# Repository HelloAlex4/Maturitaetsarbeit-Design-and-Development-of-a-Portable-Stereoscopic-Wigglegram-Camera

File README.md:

# Design and Development of a Portable Stereoscopic Wigglegram Camera

### !!!THIS IS NOT THE CURRENT VERSION OF MERGED.CAMERA, YOU SHOULD NOT COPY THIS BUILD!!!

**Author:** Alexander Rieser

**Project Type:** Maturitätsarbeit (25/26)

**Supervisor:** Madlaina Holler

**Expert:** Patrick Habegger

## Abstract

This Maturitätsarbeit details the design, development, and implementation of a custom-built, portable stereoscopic camera capable of capturing animated wigglegrams. While the wigglegram effect has traditionally been limited to specialized analog film cameras or bulky adapters, this project represents the world's first digital wigglegram camera outside of a few private prototypes. The camera utilizes four horizontally aligned camera modules controlled by multiple processors to capture the wigglegrams. The device surpasses most of its initial goals, such as a synchronization between the first and last camera capture of less than 16 ms. This document extensively details both the technical architecture of the device and the development process. Despite multiple identified limitations like the image resolution and quality, the final product serves as a successful proof-of-concept and a baseline for further improvement.

## Project Overview

This project aims to fill a gap in the market by providing a self-contained, handheld device capable of capturing and processing digital stereoscopic images (wigglegrams) without the need for analog film or bulky adapters. The camera captures four simultaneous images from slightly different perspectives and processes them into an animated GIF that loops back and forth to create a 3D depth effect.

## Features

* **Simultaneous Capture:** Utilizes four horizontally aligned OV5640 camera modules with a synchronization delay of less than 16ms between the first and last frame.

* **Digital Workflow:** Instant preview of captured images and on-device processing of wigglegrams.

* **Portable Design:** Handheld, custom 3D-printed ABS housing with anodized aluminum covers.

* **Touchscreen Interface:** Integrated display running a Flutter-based UI for live preview, gallery browsing, and settings.

* **Battery Power:** Integrated 2-cell Li-ion battery with USB-C charging and telemetry.

## System Architecture

The device is built on a multi-PCB architecture governed by a Raspberry Pi Compute Module 4 and four STM32 microcontrollers.

### Hardware

* **Main PCB:** Acts as the central hub connecting the Raspberry Pi CM4 and the four STM32H743VIT6 microcontrollers. It manages high-speed USB communication and connects the camera modules via DCMI.

* **Power PCB:** Manages power distribution, converting battery voltage (7.2V - 7.8V) into regulated rails (5V, 3.3V, 2.8V, 1.5V). It handles USB-C power negotiation and battery charging.

* **Sensors:** 4x OV5640 Camera Modules arranged with a fixed lens-to-lens distance.

### Software Stack

The software is distributed across three primary layers:

1. **User Interface (Flutter):** Handles user interactions, live preview rendering, and the image gallery on the Raspberry Pi.

2. **Background Processes (Python/C):** Runs on the Raspberry Pi; manages camera synchronization, image processing (GIF generation), and hardware interfacing (fan control, battery monitoring).

3. **Embedded Firmware (C/C++):** Runs on the four STM32 microcontrollers; handles low-level hardware abstraction, DCMI interfacing, and image transmission via USB.

## Development & Testing

The project utilized a "fail-fast" empirical approach, prioritizing rapid physical prototyping. Testing confirmed the camera achieves a between-frame capture time of less than 16ms, ensuring sharp images even with moving subjects. The assembly features a modular design with a 3D-printed chassis and custom heat-dissipation solutions.

## License

[Attribution-NonCommercial 4.0 International]

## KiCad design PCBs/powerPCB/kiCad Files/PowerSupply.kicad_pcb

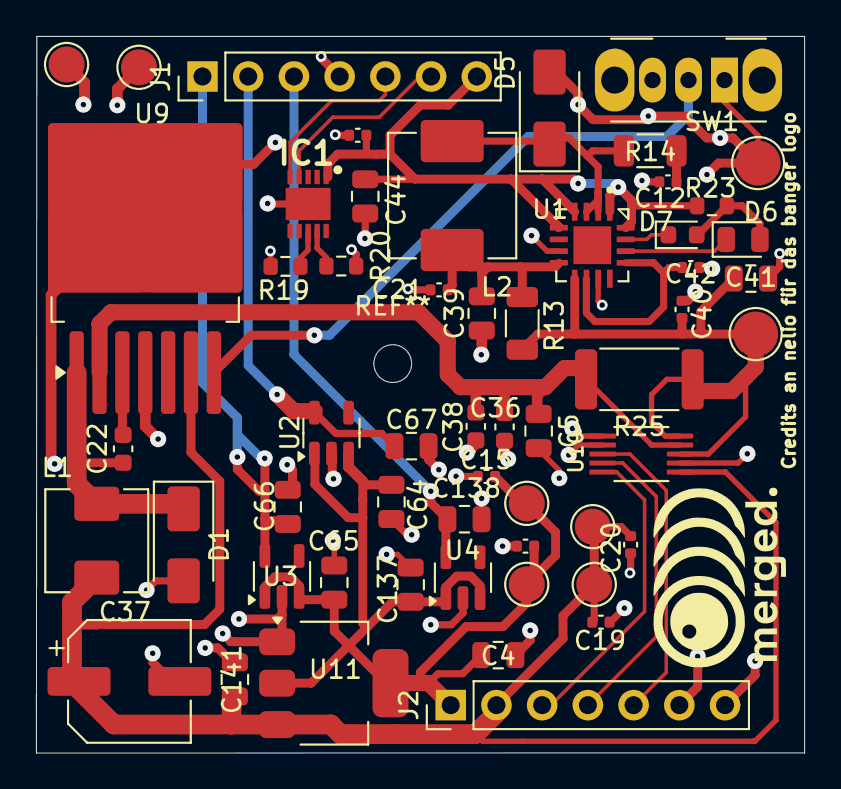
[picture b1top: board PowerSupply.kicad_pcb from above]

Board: 2 copper layers, 42.7 x 39.8 mm, 56 parts (0 on the bottom side), 24 nets.

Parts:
C4, C5: 22uF; C_0805_2012Metric
C12, C15, C16, C19, C20, C21, C40, C42, C43: 0.1uF; C_0402_1005Metric
C22: 10nF; C_0603_1608Metric
C36, C38: 6.8uF; C_0603_1608Metric
C37: 180uF; CP_Elec_6.3x5.9
C39, C41, C44: 10uF; C_0805_2012Metric
C64, C65, C66, C67, C137, C138, C141: 1uF; C_0805_2012Metric
D1: SS38; D_SMA
D5: D_Filled; D_SMA
D6: LED; LED_0805_2012Metric
D7: LED; LED_0603_1608Metric
IC1: HUSB238; SON50P300X300X80-11N-D
J1, J2: Conn_01x07_Pin; PinHeader_1x07_P2.54mm_Vertical
L1: 4.7uH inductor; L_APV_APH0530
L2: 10uH; L_Changjiang_FXL0630
R13: 0.06Ohm; R_1206_3216Metric
R14: 3 Ohm; R_1206_3216Metric
R19: 10k; R_0603_1608Metric
R20: 7.5kOhm; R_0603_1608Metric
R23: 470Ohm; R_0603_1608Metric
R25: R_Shunt; R_2512_6332Metric
SW1: SW_DPST_x2; SW_Slide_SPDT_Angled_CK_OS102011MA1Q
TP10, TP18: battery testpoint; TestPoint_Pad_D2.5mm
TP13, TP14, TP16, TP17, TP19, TP20: TestPoint; TestPoint_Pad_D2.0mm
U1: TP5100; QFN65P400X400X90-17N
U2, U4: MICRONE(Nanjing Micro One Elec) ME6212C28M5G; SOT-23-5
U3: Diodes Incorporated AP2112K-1.8TRG1; SOT-23-5
U9: LM22678TJ-5.0/NOPB; TO-263-7_TabPin8
U10: INA226AIDGSR; SOP50P490X110-10N
U11: 5v to 3.3v converter; SOT-223-3_TabPin2

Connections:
+3.3V: C4.1, C15.1, C16.2, C64.2, C65.2, C137.2, J2.1, TP16.1, TP17.1, U2.1 (IN), U2.3 (EN), U3.1 (IN), U3.3 (EN), U4.1 (IN), U4.3 (EN), U11.2 (VO)
+5V: C19.1, C20.1, C37.1, C141.2, J2.2, L1.2, TP13.1, TP19.1, U9.7 (EN), U10.6 (VS), U11.3 (VI)
/1.5v out: C138.2, J1.3, U4.5 (OUT)
/1.8v out: C66.1, J1.1, U3.5 (OUT)
/2.8v out: C67.2, J1.2, U2.5 (OUT)
/CC1: IC1.4 (CC1), J1.6
/CC2: IC1.5 (CC2), J1.5
/USB+: C43.1, C44.1, IC1.1 (VIN), J1.7, R23.1, U1.1 (VIN), U1.4 (VIN), U1.5 (VIN), U1.16 (VIN)
/battery output: C5.1, C36.1, C38.1, R25.2, U9.3 (BOOT), U10.9 (IN-)
/power SCL: J2.3, U10.5 (SCL)
/power SDA: J2.4, U10.4 (SDA)
/voltage Alert Pin: J2.5, U10.3 (ALERT)
GND: C4.2, C5.2, C12.1, C12.2, C15.2, C16.1, C19.2, C20.2, C21.1, C21.2, C36.2, C37.2, C38.2, C39.1, C39.2, C40.2, C41.2, C42.2, C43.2, C44.2, C64.1, C65.1, C66.2, C67.1, C137.1, C138.1, C141.1, D1.2 (A), D5.2 (A), IC1.11 (GND), J1.4, J2.6, J2.7, L2.1, R13.1, R14.2, R19.2, R20.2, SW1.1 (A), TP14.1, TP18.1, TP20.1, U1.7 (GND), U1.8 (VS), U1.11 (TS), U2.2 (GND), U3.2 (GND), U4.2 (GND), U9.1 (SW), U9.8, U10.1 (A1), U10.2 (A0), U10.7 (GND), U11.1 (GND)
unnamed: C22.1, D1.1 (K), L1.1, U9.4 (GND)
unnamed: D5.1 (K), L2.2, R14.1, U1.2 (LX), U1.3 (LX)
unnamed: D6.2 (A), D7.2 (A), R23.2
unnamed: D6.1 (K), U1.14 (~STDBY)
unnamed: D7.1 (K), U1.15 (~CHRG)
unnamed: IC1.9 (ISET), R20.1
unnamed: IC1.8 (VSET), R19.1
unnamed: SW1.2 (B), U9.6 (FB)
unnamed: C40.1, C41.1, R13.2, R25.1, TP10.1, U1.9 (BAT), U10.8 (VBUS), U10.10 (IN+)
unnamed: C42.1, U1.10 (VREG), U1.13 (CS)
unnamed: C22.2, U9.2 (VIN)

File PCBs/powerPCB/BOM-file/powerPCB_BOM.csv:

"Id";"Designator";"Footprint";"Quantity";"Designation";"Supplier and ref";
1;"D1";"D_SMA";1;"SS38";;;
2;"U4,U2";"SOT-23-5";2;"MICRONE(Nanjing Micro One Elec) ME6212C28M5G";;;
3;"C40,C21,C19,C43,C15,C42,C12,C20,C16";"C_0402_1005Metric";9;"0.1uF";;;
4;"C138,C66,C141,C67,C65,C64,C137";"C_0805_2012Metric";7;"1uF";;;
5;"U1";"QFN65P400X400X90-17N";1;"TP5100";;;
6;"U10";"SOP50P490X110-10N";1;"INA226AIDGSR";;;
7;"L2";"L_Changjiang_FXL0630";1;"10uH";;;
8;"U11";"SOT-223-3_TabPin2";1;"5v to 3.3v converter";;;
9;"D6";"LED_0805_2012Metric";1;"LED";;;
10;"L1";"L_APV_APH0530";1;"4.7uH inductor";;;
11;"D7";"LED_0603_1608Metric";1;"LED";;;
12;"U9";"TO-263-7_TabPin8";1;"LM22678TJ-5.0/NOPB";;;
13;"C36,C38";"C_0603_1608Metric";2;"6.8uF";;;
14;"R25";"R_2512_6332Metric";1;"R_Shunt";;;
15;"C39,C41,C44";"C_0805_2012Metric";3;"10uF";;;
16;"J2,J1";"PinHeader_1x07_P2.54mm_Vertical";2;"Conn_01x07_Pin";;;
17;"R23";"R_0603_1608Metric";1;"470Ohm";;;
18;"C37";"CP_Elec_6.3x5.9";1;"180uF";;;
19;"R19";"R_0603_1608Metric";1;"10k";;;
20;"C4,C5";"C_0805_2012Metric";2;"22uF";;;
21;"R13";"R_1206_3216Metric";1;"0.06Ohm";;;
22;"U3";"SOT-23-5";1;"Diodes Incorporated AP2112K-1.8TRG1";;;
23;"R20";"R_0603_1608Metric";1;"7.5kOhm";;;
24;"R14";"R_1206_3216Metric";1;"3 Ohm";;;
25;"C22";"C_0603_1608Metric";1;"10nF";;;
26;"SW1";"SW_Slide_SPDT_Angled_CK_OS102011MA1Q";1;"SW_DPST_x2";;;
27;"IC1";"SON50P300X300X80-11N-D";1;"HUSB238";;;
28;"D5";"D_SMA";1;"D_Filled";;;

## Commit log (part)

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2026-01-02 Add Creative Commons license
    Added the Creative Commons Attribution-NonCommercial 4.0 International Public License to the project.
2026-01-02 firstFileUpload
2026-01-02 Add README for portable stereoscopic wigglegram camera
    This README details the design and development of a portable stereoscopic wigglegram camera, including its features, system architecture, and software stack.
2026-01-02 Fix formatting issues in README.md
2026-01-02 Fix formatting in README.md
    Removed extra newline before the Sensors section.
2026-01-18 new sample images
